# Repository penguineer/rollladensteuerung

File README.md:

Rolladensteuerung
=================

Content

controller:       Relais-Controller Rollläden
manuellsteuerung: Schalter für Manuellbetrieb Rollläden
raspberry:        Software für den Kontroll-Raspy
relaiskarte:      Relais Rollläden
switchboard:      Altes Schalterboard
tuer-controller:  I2C-Bridge zur Tür-Steuerung
tuer-steuerung:   Kontrolle Motor und Türstatus-Schalter
wd-switch:        Watchdog-Switch für Reset per Raspy

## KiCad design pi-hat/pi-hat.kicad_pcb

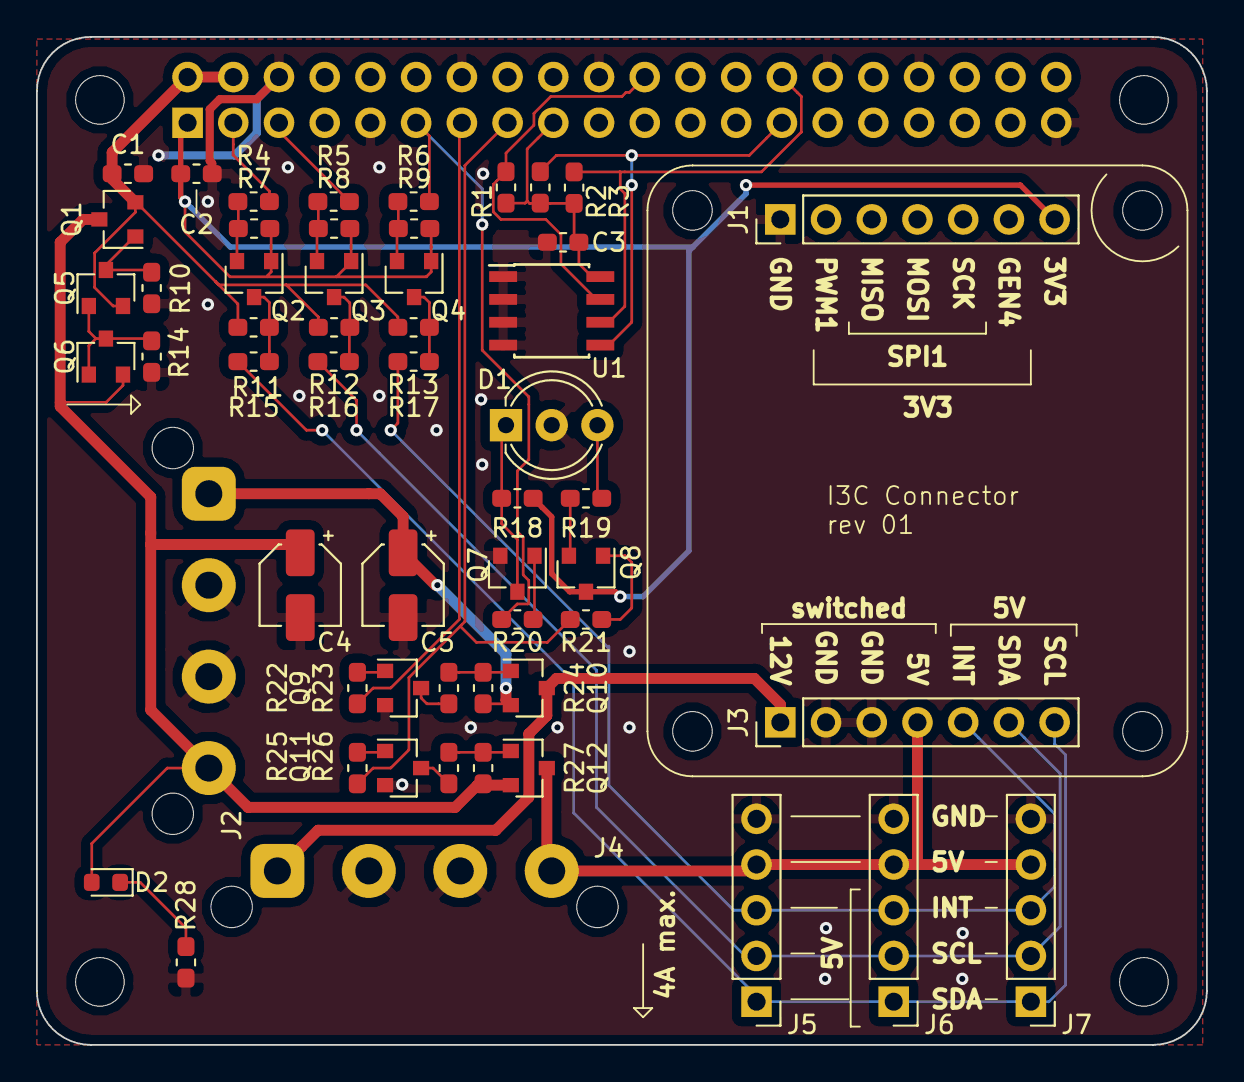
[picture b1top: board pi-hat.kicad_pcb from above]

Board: 2 copper layers, 65.0 x 56.0 mm, 64 parts (1 on the bottom side), 39 nets.

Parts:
C1, C2, C3: 100n; C_0603_1608Metric_Pad1.05x0.95mm_HandSolder
C4, C5: 47u; CP_Elec_4x4.5
D1: LED5 RG-3; LED_D5.0mm-3
D2: LED; LED_0603_1608Metric
J1, J3: Conn_01x07_Male; PinHeader_1x07_P2.54mm_Vertical
J2, J4: Conn_01x04_Male; MOLEX-HDD-PWR-horizontal
J5, J6, J7: Conn_01x05_Male; PinHeader_1x05_P2.54mm_Vertical
MK1, MK2, MK7, MK8: M2.5; MountingHole_2.7mm_M2.5
MK3, MK4, MK5, MK6: 2.0; MountingHole_2.2mm_M2_DIN965
P1: Conn_02x20_Odd_Even; PinSocket_2x20_P2.54mm_Vertical
Q1, Q10, Q12: AO 3415A; SOT-23
Q2, Q3, Q4: BSS138; SOT-23
Q5, Q6: BC 807-25; SOT-23
Q7, Q8, Q9, Q11: BC 818-25; SOT-23
R1, R7, R8, R9, R11, R12, R13, R14, R24, R27: 10K; C_0603_1608Metric_Pad1.05x0.95mm_HandSolder
R2, R3: 3K9; C_0603_1608Metric_Pad1.05x0.95mm_HandSolder
R4, R5, R6, R15, R16, R17, R23, R26: 10R; C_0603_1608Metric_Pad1.05x0.95mm_HandSolder
R10: 47K; C_0603_1608Metric_Pad1.05x0.95mm_HandSolder
R18, R19, R28: 150R; C_0603_1608Metric_Pad1.05x0.95mm_HandSolder
R20, R21, R22, R25: 330R; C_0603_1608Metric_Pad1.05x0.95mm_HandSolder
U1: M24C02-WMN; SOIC-8_3.9x4.9mm_P1.27mm

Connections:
+3.3VA: C3.1, P1.17, R1.1, R2.1, R3.1, U1.8
+3V3: C2.1, J1.7, P1.1, Q2.1, Q3.1, Q4.1, Q8.3, R7.1, R8.1, R9.1, R18.1
+5V: C1.1, P1.2, P1.4, Q1.2, Q5.2, R11.1, R12.1, R13.1
+5VA: J3.4, J4.4, J5.4, J6.4, J7.4, Q12.3
+5VP: C4.1, D2.2, J2.4, Q1.3, Q6.2, Q12.2, R27.1
+12V: C5.1, J2.1, Q10.2, R24.1
+12VA: J3.1, J4.1, Q10.3
ACTIVATE_5V: P1.15, R21.1, R25.2
ACTIVATE_12V: P1.13, R22.2
GND: C1.2, C2.2, C3.2, C4.2, C5.2, D1.2, J1.1, J2.2, J2.3, J3.2, J3.3, J4.2, J4.3, J5.5, J6.5, J7.5, P1.6, P1.9, P1.14, P1.20, P1.25, P1.30, P1.34, P1.39, Q7.2, Q9.2, Q11.2, R10.2, R14.2, R28.2, U1.1, U1.2, U1.3, U1.4
ID_SC: P1.28, R3.2, U1.6
ID_SD: P1.27, R2.2, U1.5
ID_WP: P1.22, R1.2, U1.7
INT: P1.11, R6.2, R20.2
INT_5V: J3.5, J5.3, J6.3, J7.3, R17.1
unnamed: D1.1, Q7.3, R18.2
unnamed: D1.3, R19.2
unnamed: D2.1, R28.1
unnamed: Q2.2, R4.1, R7.2
unnamed: Q2.3, R11.2, R15.2
unnamed: Q3.2, R5.1, R8.2
unnamed: Q3.3, R12.2, R16.2
unnamed: Q4.2, R6.1, R9.2
unnamed: Q4.3, R13.2, R17.2
unnamed: Q5.1, Q6.1, Q6.3, R14.1
unnamed: Q1.1, Q5.3, R10.1
unnamed: Q7.1, R20.1
unnamed: Q8.1, R21.2
unnamed: Q8.2, R19.1
unnamed: Q9.1, R22.1
unnamed: Q9.3, R23.2
unnamed: Q10.1, R23.1, R24.2
unnamed: Q11.1, R25.1
unnamed: Q11.3, R26.2
unnamed: Q12.1, R26.1, R27.2
SCL: P1.5, R5.2
SCL_5V: J3.6, J5.2, J6.2, J7.2, R16.1
SDA: P1.3, R4.2
SDA_5V: J3.7, J5.1, J6.1, J7.1, R15.1

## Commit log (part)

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2012-09-11 initial commit of schematics
2012-09-11 added .gitignore to ignore eagle autosave-files; removed old autosave-files
2012-09-11 removed eagle.epf (local config file)
2012-09-16 added schaltplan_v2
2012-09-17 schaltplan_v2 finalized
2012-09-17 more fixes
2012-11-24 change 9pin connector to sub-d
2013-01-01 initial schematic commit, copy from old repo
2013-01-02 added correct connectors
2013-01-02 replaced another connector
2013-01-03 more layout fixes
2013-01-03 fixed ground areas
2013-01-27 minor layout fixes
2013-01-27 just another fix
2013-01-28 24367dfa: add drill holes and replace changed relais
2013-01-28 minor fixes again
2013-01-30 rerouting and fixed drill hole distances
2013-01-31 fix ERC issues and schematic, reroute some signals
    overall connection was lost due to some signal renamings, some parts
    were not connected at all. additionally added restrict area around drill
    holes
2013-01-31 fix wrong connections in schematics
    transitor pins were connected wrong and resistors are not diodes!
2013-02-05 fix some paths on hv part
2013-02-20 add *.pdf to .gitignore
2013-03-01 add pinout.txt
2013-03-03 add swichboard schematic and board
2013-03-03 add text/drillholes/copper fill to swichboard
2013-05-22 Relaiskarte in Unterordner verschoben
2013-05-22 Firmware minimal version
2013-05-25 Controller Schematics Controller-Boeard erster entwurf
2013-05-25 Routing erster Versuch
2013-05-26 Anpassung: SHCP und STCP verbunden
2013-05-26 PLatinenlayout fertig
2013-05-29 Layout-Tweaks, alle LEDs nun nebeneinander
2013-06-05 Mehr Abstand in der GND-Isolation
2013-06-06 * Platinenlayout nochmal angepasst (hauptsächlich Leiterbahndicken) * dritten Bus-Stecker vorgesehen
2013-06-09 Änderungen an PIN-Belegung
2013-06-12 Korrekte Ansteuerung der Ausgänge und Zuordnung Adresse/Ausgang
2013-06-12 rücksetz-fehler bleibt :/
2013-06-13 Fehler gefixt
2013-06-15 initial hardware axis
2013-06-16 Version 2
2013-06-16 Skel Firmware für Manuellsteuerung
2013-07-31 Entprellung für den Manuell-Schalter
2013-07-31 Blinken eingebaut
2013-08-01 Beeper eingefügt
2013-08-01 Timing-Werte angepasst
2013-08-02 * use attiny44 (more RAM) * debugging for serial register read-out
2013-08-02 SR works :)
2013-08-02 Delay nach PL wird nicht benötigt
2013-08-02 Beep Patterns
2013-08-02 Aufräumarbeiten
2013-08-02 * pull-up am schalter intern gesetzt * spielkram
2013-08-02 i3c-Interrupt-Handling
2013-08-06 Schematics und Board für Manuellsteuerung
2013-08-06 controller.brd hier nicht benötigt
2013-08-08 Repository-Inhalt in eigenem Verzeichnis -> für Merge mit netz39_rollladensteuerung
2013-08-08 * README ins Hauptverzeichnis * swichboard -> switchboard
2013-09-01 Firmware an geänderte Pin-Belegung angepasst
2013-09-02 Anpassungen für provisorische Rollladensteuerung
2013-09-02 Doku Output Status Byte
2013-09-02 Doku Switch Array Status
2013-09-02 * adjusted beeper handling to new status bytes * use switch array * adjusted initialization routine * adjusted block switch LED * adjust status LED * use macros for port access
2013-09-03 Bugfixing
2013-09-03 Bug finally fixed :)
2013-09-19 Bisheriges Shell-Script
2013-09-19 gitignore für shuttercontrol
2013-09-19 Skeleton
2013-09-19 *.elf aus Makefile entfernt
2013-10-04 Shuttercontrol: bisherige Funktionen in eigene functions ausgelagert
2013-10-04 Beep
2013-10-04 LED manual light control
2013-10-04 Parity erstmal deaktiviert
2013-10-04 Check all switches.
2013-10-04 Simple result check routine
2013-10-04 Error check on I2C command and result transmission
2013-10-05 Correct switch assignments
2013-10-05 Added the controller again
2013-10-05 manual mode switch
2013-10-05 block interrupts when cycling register
2013-10-07 more stuff
2013-10-24 Switch-Adressen korrigiert
2013-10-25 Correct use of functions; C lets you do any crap!
2013-10-26 Startup-Sequence
2013-10-26 newline at end of file
2013-11-08 SVGs für Gehäusefräspfade
2013-11-08 Aufhängung
2013-11-09 The right way to measure time millis ^^
2013-11-09 Keep the shutter going for a while if switch is held for two seconds.
2013-11-23 Switch für den Watchdog
2013-11-24 * Bohrlöcher xD * kleine Verbesserungen im Platinenlayout
2013-11-24 erster Entwurf Tür-Steuerung
2013-11-25 USB-Stromversorgung
2013-12-01 Werte für die Kondensatoren angegeben
2013-12-04 Schaltung Türsteuerung ergänzt
2013-12-04 Erster Entwurf Board Türsteuerung
2013-12-05 * Kleine Anpassungen in der Schaltung * Layout der Peripherie
2013-12-06 Alex' Verbesserungen eingearbeitet und Layout fortgesetzt
2013-12-07 Anschlussklemmen angepasst
2013-12-10 Quartz-Positionierung gemäß Application Note
2013-12-15 Tür-Controller (I2C-Gegenstelle zur Tür-Steuerung)
2013-12-16 Mindesgrößen der Pads und Vias angepasst
2013-12-18 SENSE -> GND
2013-12-19 Korrigiertes Design
2013-12-21 WD-Switch jetzt mit Relais
2013-12-22 Korrigiertes M4-Relais eingesetzt
2014-01-02 Integrierter I³C-Pegeladapter mit WatchDog-Switch
2014-01-03 Zustands-LED eingebaut
2014-01-03 Rollladen-Script wird nicht mehr gebraucht
2014-01-03 Übrige Leiterbahn entfernt
2014-01-05 Watchdog ein/ausschalten über Pin 4 (GPIO 23)
2014-01-05 Fehlendes Routing fehlt m(
2014-01-15 Anschlussklemmen durch die richtigen Typen ersetzt und Mini-Tweaks
2014-01-16 Letzte Anpassungen vor dem Ätzen
2014-01-22 andere Holes, Beschriftung, eine Leiterbahn leicht verschoben
2014-01-22 Beschriftung und Bohrlöcher
2014-01-29 Dokumentation Tür-Gehäuse von Hichi
2014-01-30 add raspberry/i2cbridge, untested
2014-01-31 * Ports setzen * LED-Ansteuerung
2014-01-31 i2cbridge: fix Makefile
2014-01-31 i2cbridge: fix sun_family and addrsize
2014-01-31 i2cbridge: fix i2c handling
2014-01-31 i2cbridge: fix i2c poll bug
2014-01-31 i2cbridge: add reuse_sockaddr
2014-01-31 i2cbridge: remove superfluous buf variable
2014-01-31 i2cbridge: add simple client
2014-01-31 i2cbridge: remove client binary, add to .gitignore
2014-01-31 it works for now; erster Prototyp
2014-01-31 Aktives Bremsen
2014-01-31 Make-Target für Fuses
2014-02-01 i2cbridge: add unix client
2014-02-01 Überflüssige Funktion entfernt Einteilung in Module
2014-02-01 Feststellen des Schloss-Status anhand der Sensoren
2014-02-01 Blink-Steuerung für die LEDs
2014-02-01 Shuttercontrol in eigenes Subdir verschoben
2014-02-02 - ein paar Code-Tweaks - Schloss öffnen, wenn Status unklar
2014-02-03 Base version firmware Tür-Controller
2014-02-03 gitignore für tuer-controller
2014-02-03 .gitignore für tuer-steuerung
2014-02-03 Fräs-DXF für Tür-Steuerung
2014-02-05 fuse Make
2014-02-06 Shell-Script zum Einschalten
2014-02-06 * LED-Richtung geprüft * Port-Config korrigiert m( * ein paar Tests
2014-02-06 Korrektur: Tür öffnen nur bei widersprüchlichem Sensorstatus, ansonsten Status lassen (nat. auch, wenn kein Command vorliegt)
2014-02-06 1==0==1 oder so
2014-02-09 Zuverlässiges Schalten
2014-02-09 doofen Fehler korrigiert
    diese Version läuft jetzt auch auf dem Schloss
2014-02-13 Pause vor Motorfreigabe bei Schließen der Tür
2014-02-15 Asterisk-Files für die Door-Auth
2014-02-18 Use the syslog facility for relevant messages.
2014-02-23 i2cbridge ist jetzt in https://github.com/netz39/i2cbridge => nicht mehr benötigte files entfernt
2014-02-26 gitignore
2014-02-27 Log call to door-open.sh
2014-02-27 Security backup script: close the door if it is unlocked with inactive SpaceTime for more than 30 seconds
2014-02-27 * if in doubt about the SpaceTime status, engage the count-down * syslog logging
2014-02-28 Defuse the json extractor ( a bit … )
2014-02-28 Direct logging to tag "lockfailsafe"
2014-02-28 Deactivate the redundant use of the manual mode LED (which copied the nerd star)
2014-02-28 A bit of beeping und blinking
2014-02-28 Brought back the redundant LED display, but a bit more sophisticated.
2014-07-04 door sound script
2014-07-12 Doorlock Controller: Pause-Switch auf Force Close umgestellt
2014-07-12 Door control: Adapted scripts to new door controller address.
2014-07-12 Shuttercontrol: Adapted to new door controller address.
2014-07-12 Doorsound: fixed the script
2014-07-12 Tür-Schalter: Aussparung an Top
2014-07-12 Tür-Schalter: Grundlegende Skizze
2014-08-18 BAK-Files entfernt
2014-08-18 Files in ein Unterverzeichnis verschoben
2015-12-05 Asterisk abuse handling: find IP addresses
    Check the syslog for abuse messages from Asterisk and add the mentioned IP
    addresses to the UFW firewall.
    Note: This does not immediately block the address, as SIP keeps the channel
    open. Either block the address completely or restart Asterisk.
2015-12-05 Do not init the I2C every time a command is called.
2015-12-05 Asterisk abuse: Cut an abusing connection
2016-04-23 Debounce demo
2016-04-23 Gitignore for the debouncing part
2016-04-30 Debounce library code quality
    Add fixes regarding https://github.com/netz39/rollladensteuerung/pull/1#issuecomment-214857090
2016-04-30 Debounce demo code quality
    Add fixes regarding https://github.com/netz39/rollladensteuerung/pull/1#issuecomment-214857090
2016-07-10 Debounce: Correct pattern for button down and up
    Set the correct patterns for debounce_is_button_down and debounce_is_button_up.
    (The values were mixed up.)
2016-07-10 Remove unused function check_status_light
2016-07-10 Add debounce histories and updates
2016-07-10 State Machine documentation
2016-07-10 Add debounce lib to make file
2016-07-14 bringt debouncing into effect w/ new state machine
    General overhaul:
    * use the Input State Byte (ISB) to store the local state
    * output ports are set based on the ISB
    * very slim timer ISR
    * twi_idle_callback checks for input updates
    * be sensitive with the interrupt-enable flag
2016-07-14 Add document status to state machine documentation
2016-08-08 Adapt to changed I2C and door status bit
2016-08-08 Doorstate: detect and log changes in door state
2016-08-08 Doorstate: Send MQTT messages
    Topic is Netz39/Things/Door/Events,
    c.f. http://www.netz39.de/wiki/projects:2014:gatekeeper:mqtt
2016-08-09 Doorstate: Reconnect to MQTT
2017-03-12 Shuttercontrol: Add mosquitto lib to Makefile
2017-03-12 Shuttercontroll: mosquitto init/destroy and loop
2017-03-12 Shuttercontrol: disable manual-mode LED
2018-01-06 doorstate: Add button status messages to MQTT
2018-01-06 doorstate: MQTT send as distinct function
2018-12-30 PiHat: first draft revision
2019-01-06 PiHat: 2nd revision
    * Checked and adapted MOSFET high-side switches
    * remove J6 for space and fix mounting hole
    * Fix Molex connectors
    * Capacitors
    * Extension board positions
    * General layout
2019-01-06 Final fixes
    * make sheet bigger (A3) to fix everything nicely
    * fix INT LED to be low active
    * fix molex holes
    * fix base resistors
2019-01-07 Add matching resistors to I3C lines
2019-01-19 Remove some level shifters
    The level shifters made only sense for I3C - removed the rest.
2019-01-27 Run RenumKicadPCB to sort designators
    https://github.com/penguineer/RenumKicadPCB
2019-01-27 Final pass for board fillings
2019-07-14 Basic MQTT implementation
2019-07-14 Door state check and callback
2019-07-14 Post door status to MQTT
2019-07-14 React to MQTT commands
    Commands on /Command
    door_open, door_close
2019-07-20 Fix: Zero return from I3C is error condition
2019-07-20 Add commands as constants
2019-07-20 Use syslog
2019-07-21 Don't log SMBus errors
    Those errors can be treated and only fill up the log.
2019-07-26 Added gitignore for pycharm python project
2019-07-26 Add a lock actor
2019-07-26 Add Signal and Loop handling
2019-07-26 Integrate everything
2019-07-26 Add a Space status observer
2019-07-26 Add the actual Watchdog
2019-07-26 Add a door lock observer
2019-10-27 Pre-seed the lock state
    Don't block in BOOT if the lock state is unknown.
    As a fallback, we assume that the lock is open.
2019-10-27 Clear beeps when leaving countdown state
2019-10-27 Add the actual beep train
2019-10-27 Send MQTT command for beep
2019-10-27 Add infrastructure for beep scheduling
2019-10-27 Initial shuttercontrol service with beep
